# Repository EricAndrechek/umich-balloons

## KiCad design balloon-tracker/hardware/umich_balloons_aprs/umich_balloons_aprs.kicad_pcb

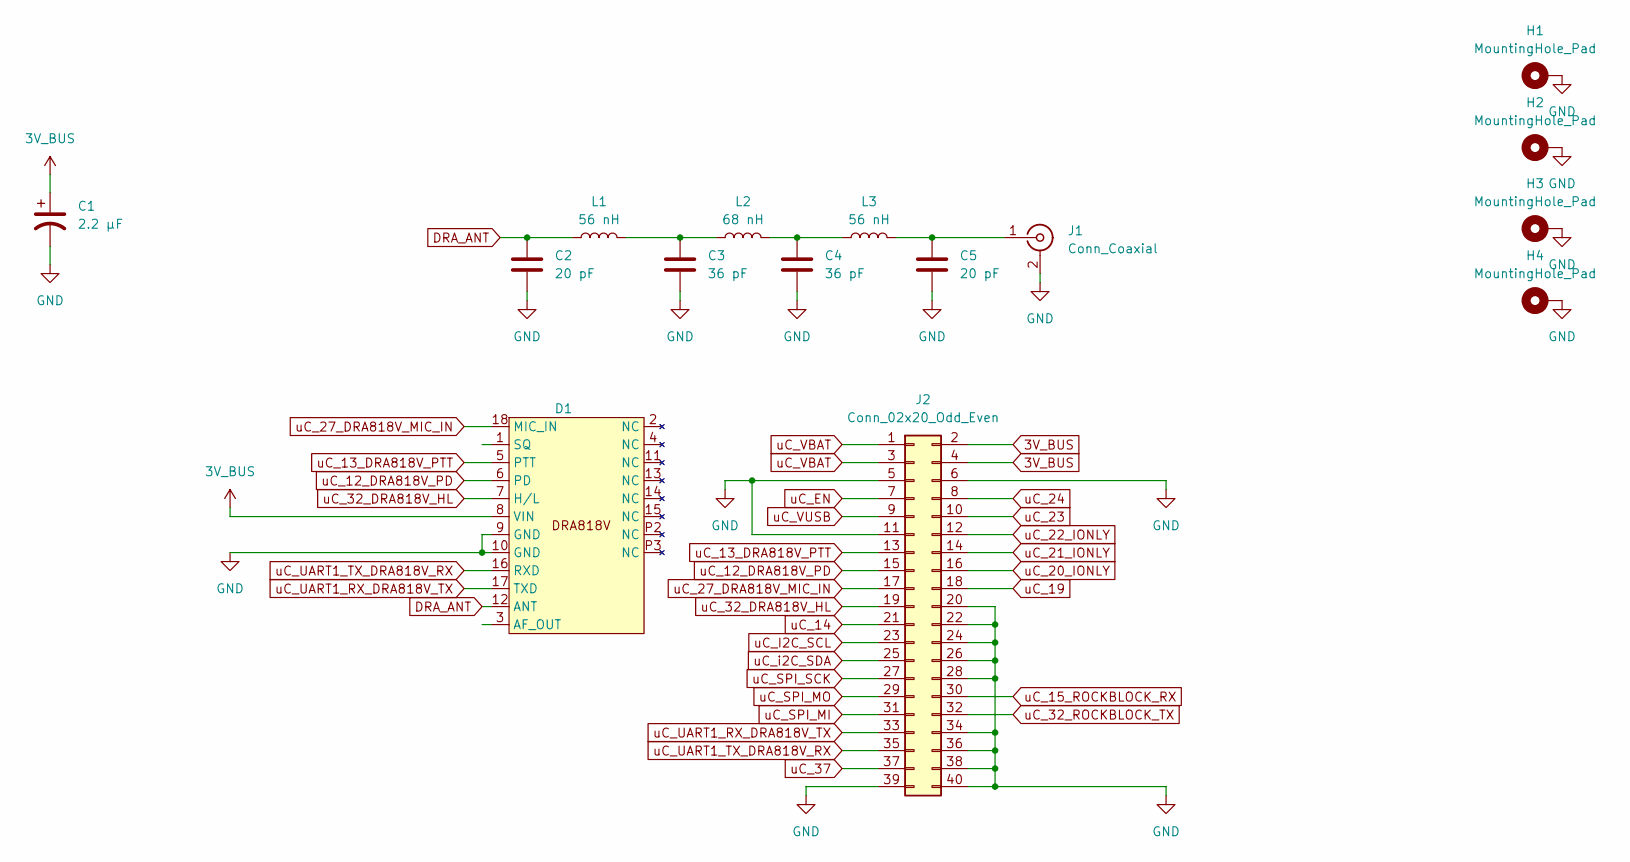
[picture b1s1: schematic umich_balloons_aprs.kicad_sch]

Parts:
C1: 2.2 µF; CP_Radial_D5.0mm_P2.00mm
C2, C5: 20 pF; C_1206_3216Metric_Pad1.33x1.80mm_HandSolder
C3, C4: 36 pF; C_1206_3216Metric_Pad1.33x1.80mm_HandSolder
D1: DORJI_DRA818V
H1, H2, H3, H4: MountingHole_Pad; MountingHole_3.2mm_M3_Pad_Via
J1: Conn_Coaxial; SMA_Wurth_60312002114503_Vertical
J2: Conn_02x20_Odd_Even; PinHeader_2x20_P2.54mm_Vertical
L1, L3: 56 nH; L_1206_3216Metric_Pad1.22x1.90mm_HandSolder
L2: 68 nH; L_1206_3216Metric_Pad1.22x1.90mm_HandSolder

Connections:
3V_BUS: C1.1, D1.8 (VIN), J2.2, J2.4
DRA_ANT: C2.1, D1.12 (ANT), L1.1
GND: C1.2, C2.2, C3.2, C4.2, C5.2, D1.9 (GND), D1.10 (GND), H1.1, H2.1, H3.1, H4.1, J1.2 (Ext), J2.5, J2.6, J2.11, J2.20, J2.22, J2.24, J2.26, J2.28, J2.34, J2.36, J2.38, J2.39, J2.40
unnamed: C3.1, L1.2, L2.1
unnamed: C4.1, L2.2, L3.1
unnamed: C5.1, J1.1 (In), L3.2
uC_12_DRA818V_PD: D1.6 (PD), J2.15
uC_13_DRA818V_PTT: D1.5 (PTT), J2.13
uC_14: J2.21
uC_15_ROCKBLOCK_RX: J2.30
uC_19: J2.18
uC_20_IONLY: J2.16
uC_21_IONLY: J2.14
uC_22_IONLY: J2.12
uC_23: J2.10
uC_24: J2.8
uC_27_DRA818V_MIC_IN: D1.18 (MIC_IN), J2.17
uC_32_DRA818V_HL: D1.7 (H/L), J2.19
uC_32_ROCKBLOCK_TX: J2.32
uC_37: J2.37
uC_EN: J2.7
uC_I2C_SCL: J2.23
uC_SPI_MI: J2.31
uC_SPI_MO: J2.29
uC_SPI_SCK: J2.27
uC_UART1_RX_DRA818V_TX: D1.17 (TXD), J2.33
uC_UART1_TX_DRA818V_RX: D1.16 (RXD), J2.35
uC_VBAT: J2.1, J2.3
uC_VUSB: J2.9
uC_i2C_SDA: J2.25

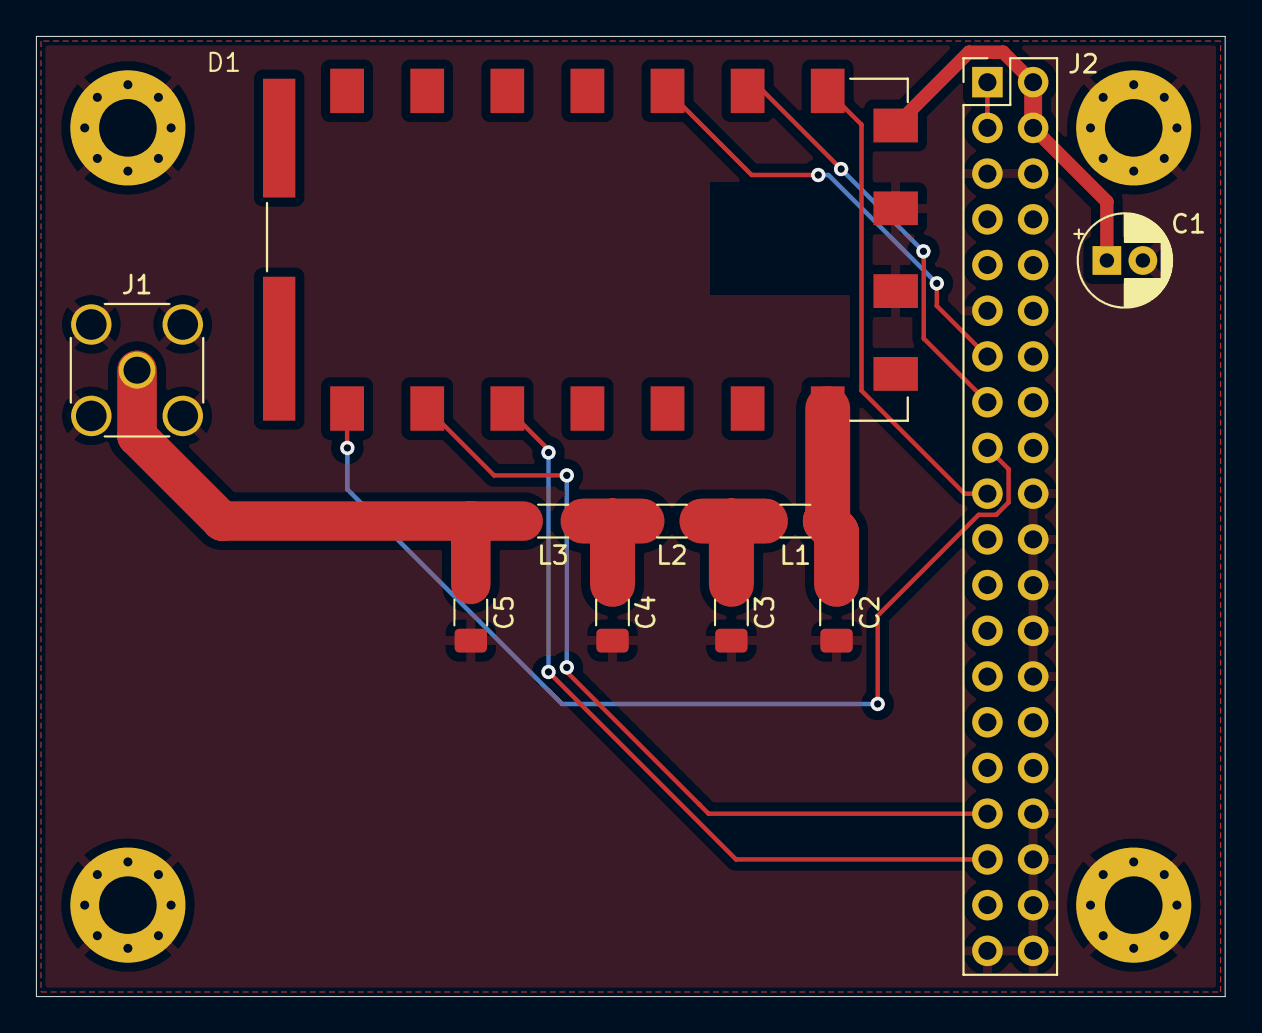
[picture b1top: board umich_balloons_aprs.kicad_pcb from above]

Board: 2 copper layers, 66.0 x 53.3 mm, 15 parts (0 on the bottom side), 13 nets.

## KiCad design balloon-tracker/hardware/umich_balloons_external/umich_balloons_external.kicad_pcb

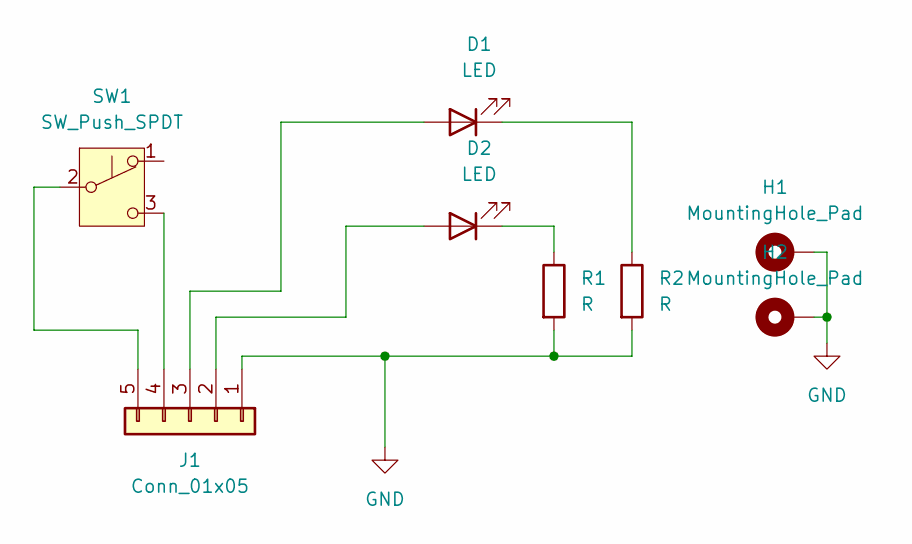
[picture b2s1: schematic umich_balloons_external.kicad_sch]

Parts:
D1, D2: LED; LED_D5.0mm
H1, H2: MountingHole_Pad; MountingHole_3.2mm_M3_Pad_Via
J1: Conn_01x05; JST_EH_B5B-EH-A_1x05_P2.50mm_Vertical
R1, R2: R; R_Axial_DIN0207_L6.3mm_D2.5mm_P10.16mm_Horizontal
SW1: SW_Push_SPDT; PC712A

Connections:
GND: H1.1, H2.1, J1.1, R1.2, R2.2
unnamed: D1.2 (A), J1.3
unnamed: D1.1 (K), R2.1
unnamed: D2.2 (A), J1.2
unnamed: D2.1 (K), R1.1
unnamed: J1.4, SW1.3 (C)
unnamed: J1.5, SW1.2 (B)

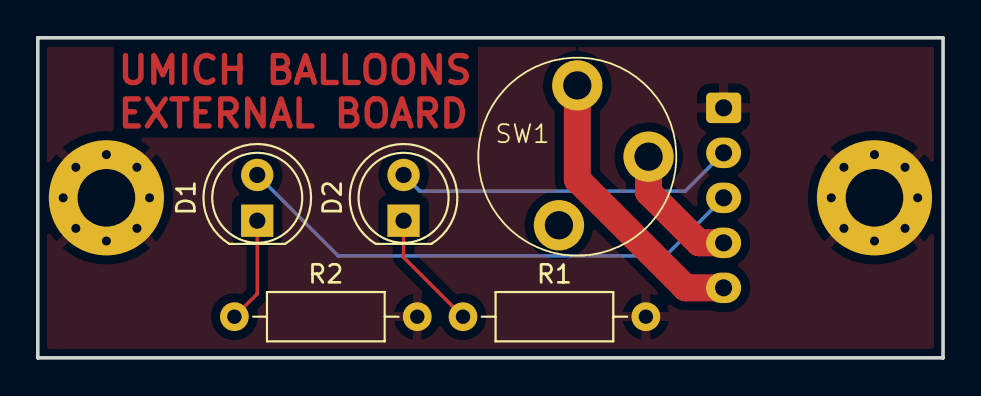
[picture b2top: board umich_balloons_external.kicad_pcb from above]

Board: 2 copper layers, 50.3 x 17.8 mm, 8 parts (1 on the bottom side), 7 nets.

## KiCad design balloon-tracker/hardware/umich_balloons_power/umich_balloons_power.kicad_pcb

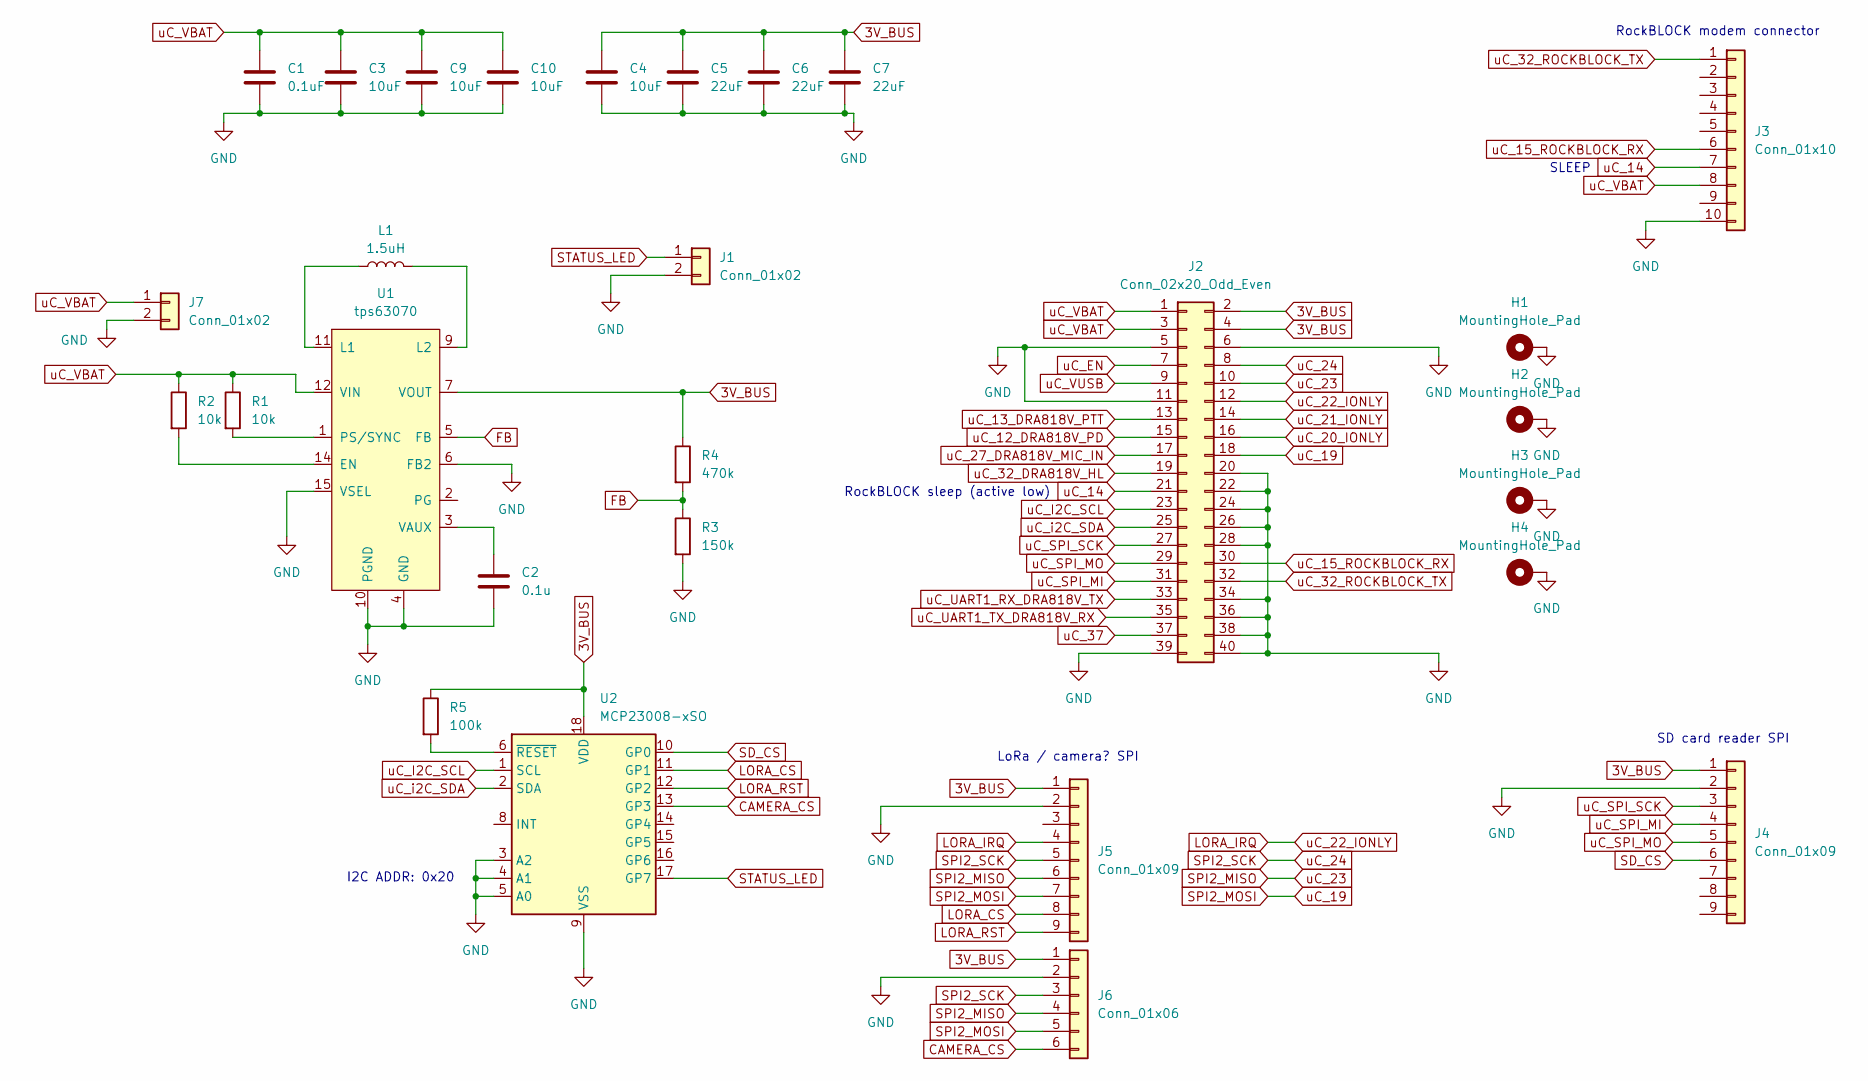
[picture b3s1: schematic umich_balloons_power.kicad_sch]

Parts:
C1: 0.1uF; C_0603_1608Metric; LCSC C14663
C2: 0.1u; C_0805_2012Metric; LCSC C1711
C3, C9, C10: 10uF; C_0805_2012Metric; LCSC C694230
C4: 10uF; C_0603_1608Metric; LCSC C386081
C5, C6, C7: 22uF; C_0805_2012Metric; LCSC C258782
H1, H2, H3, H4: MountingHole_Pad; MountingHole_3.2mm_M3_Pad_Via
J1: Conn_01x02; PinHeader_1x02_P2.54mm_Vertical
J2: Conn_02x20_Odd_Even; PinHeader_2x20_P2.54mm_Vertical
J3: Conn_01x10; Molex_PicoBlade_53047-1010_1x10_P1.25mm_Vertical
J4, J5: Conn_01x09; PinHeader_1x09_P2.54mm_Vertical
J6: Conn_01x06; PinHeader_1x06_P2.54mm_Vertical
J7: Conn_01x02; JST_XH_S2B-XH-A_1x02_P2.50mm_Horizontal
L1: 1.5uH; L_Coilcraft_XxL4020; LCSC C3033018
R1, R2: 10k; R_0603_1608Metric; LCSC C25804
R3: 150k; R_0603_1608Metric; LCSC C22807
R4: 470k; R_0603_1608Metric; LCSC C23178
R5: 100k; R_0603_1608Metric; LCSC C25803
U1: tps63070; VQFN-HR-15; LCSC C109322
U2: MCP23008-xSO; SOIC-18W_7.5x11.6mm_P1.27mm; LCSC C92253

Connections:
3V_BUS: C4.1, C5.1, C6.1, C7.1, J2.2, J2.4, J4.1, J5.1, J6.1, R4.1, R5.1, U1.7 (VOUT), U2.18 (VDD)
CAMERA_CS: J6.6, U2.13 (GP3)
FB: R3.1, R4.2, U1.5 (FB)
GND: C1.2, C2.2, C3.2, C4.2, C5.2, C6.2, C7.2, C9.2, C10.2, H1.1, H2.1, H3.1, H4.1, J1.2, J2.5, J2.6, J2.11, J2.20, J2.22, J2.24, J2.26, J2.28, J2.34, J2.36, J2.38, J2.39, J2.40, J3.10, J4.2, J5.2, J6.2, J7.2, R3.2, U1.4 (GND), U1.6 (FB2), U1.10 (PGND), U1.15 (VSEL), U2.3 (A2), U2.4 (A1), U2.5 (A0), U2.9 (VSS)
LORA_CS: J5.8, U2.11 (GP1)
LORA_IRQ: J2.12, J5.4
LORA_RST: J5.9, U2.12 (GP2)
unnamed: R2.2, U1.14 (EN)
unnamed: L1.1, U1.11 (L1)
unnamed: L1.2, U1.9 (L2)
unnamed: R1.2, U1.1 (PS/SYNC)
unnamed: C2.1, U1.3 (VAUX)
unnamed: R5.2, U2.6 (~RESET)
SD_CS: J4.6, U2.10 (GP0)
SPI2_MISO: J2.10, J5.6, J6.4
SPI2_MOSI: J2.18, J5.7, J6.5
SPI2_SCK: J2.8, J5.5, J6.3
STATUS_LED: J1.1, U2.17 (GP7)
uC_12_DRA818V_PD: J2.15
uC_13_DRA818V_PTT: J2.13
uC_14: J2.21, J3.7
uC_15_ROCKBLOCK_RX: J2.30, J3.6
uC_20_IONLY: J2.16
uC_21_IONLY: J2.14
uC_27_DRA818V_MIC_IN: J2.17
uC_32_DRA818V_HL: J2.19
uC_32_ROCKBLOCK_TX: J2.32, J3.1
uC_37: J2.37
uC_EN: J2.7
uC_I2C_SCL: J2.23, U2.1 (SCL)
uC_SPI_MI: J2.31, J4.4
uC_SPI_MO: J2.29, J4.5
uC_SPI_SCK: J2.27, J4.3
uC_UART1_RX_DRA818V_TX: J2.33
uC_UART1_TX_DRA818V_RX: J2.35
uC_VBAT: C1.1, C3.1, C9.1, C10.1, J2.1, J2.3, J3.8, J7.1, R1.1, R2.1, U1.12 (VIN)
uC_VUSB: J2.9
uC_i2C_SDA: J2.25, U2.2 (SDA)

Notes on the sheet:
I2C ADDR: 0x20
RockBLOCK modem connector
RockBLOCK sleep (active low)
LoRa / camera? SPI
SLEEP
SD card reader SPI

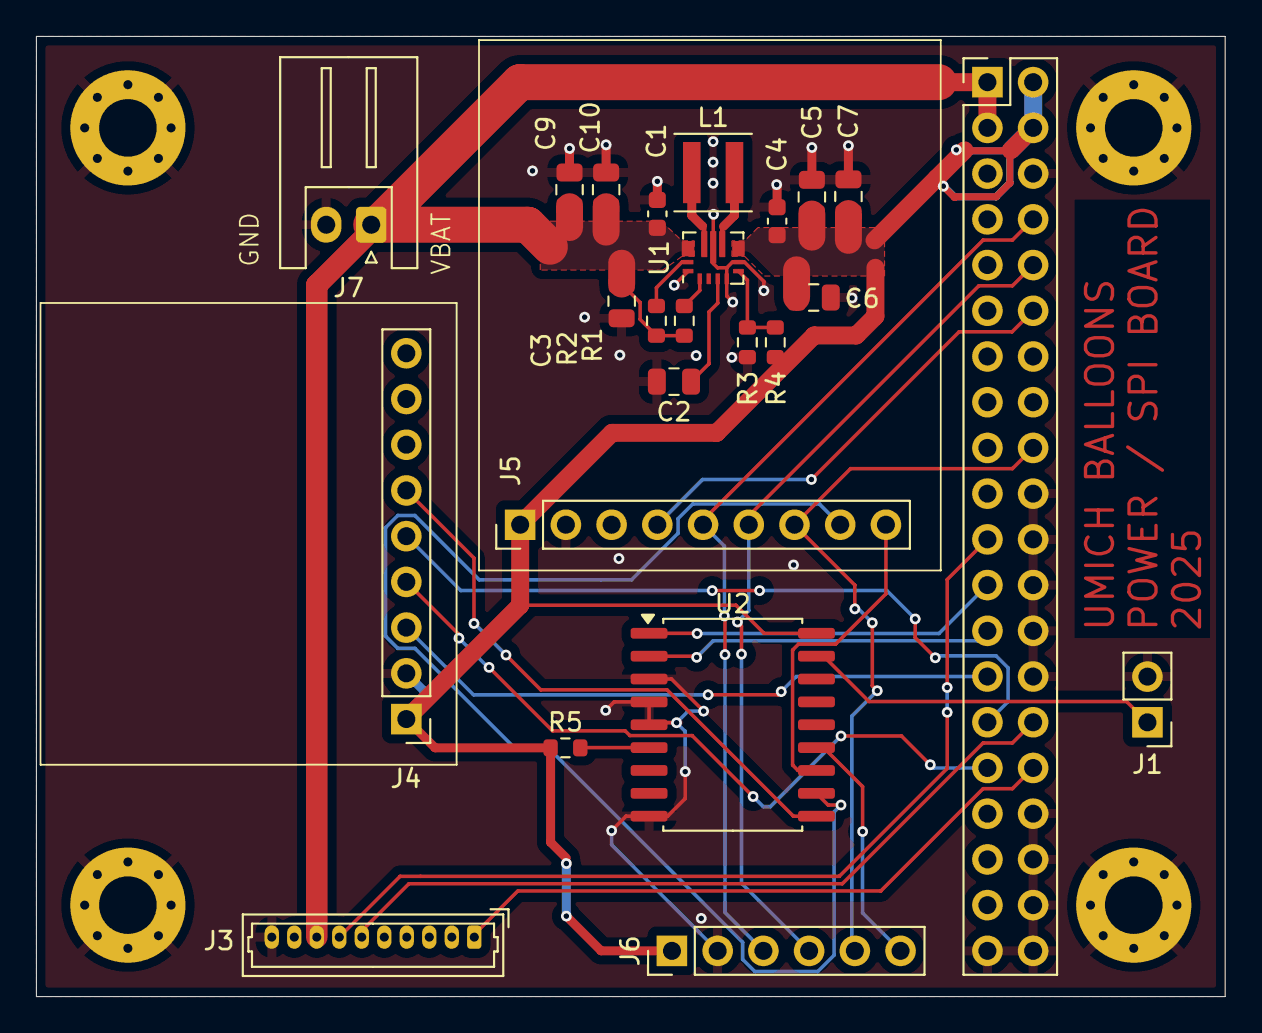
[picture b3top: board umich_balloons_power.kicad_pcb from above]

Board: 2 copper layers, 66.0 x 53.3 mm, 28 parts (0 on the bottom side), 27 nets.

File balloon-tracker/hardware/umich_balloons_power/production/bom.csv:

Designator,Footprint,Quantity,Value,LCSC Part #
C1,0603,1,0.1uF,C14663
"C10, C3, C9",0805,3,10uF,C694230
C2,0805,1,0.1u,C1711
C4,0603,1,10uF,C386081
"C5, C6, C7",0805,3,22uF,C258782
L1,L_Coilcraft_XxL4020,1,1.5uH,C3033018
"R1, R2",0603,2,10k,C25804
R3,0603,1,150k,C22807
R4,0603,1,470k,C23178
R5,0603,1,100k,C25803
U1,VQFN-HR-15,1,tps63070,C109322
U2,SOIC-18W_7.5x11.6mm_P1.27mm,1,MCP23008-xSO,C92253

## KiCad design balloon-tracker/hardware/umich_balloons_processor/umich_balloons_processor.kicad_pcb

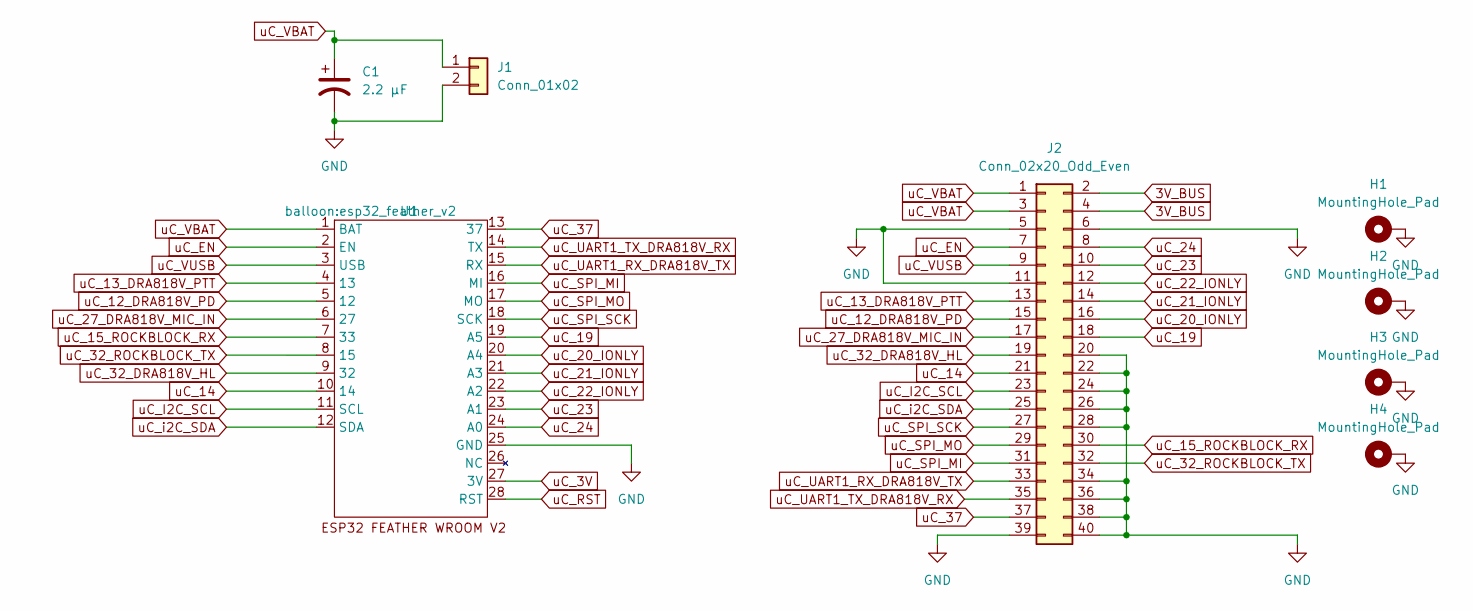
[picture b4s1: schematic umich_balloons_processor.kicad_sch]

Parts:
C1: 2.2 µF; CP_Radial_D5.0mm_P2.00mm
H1, H2, H3, H4: MountingHole_Pad; MountingHole_3.2mm_M3_Pad_Via
J1: Conn_01x02; JST_EH_S2B-EH_1x02_P2.50mm_Horizontal
J2: Conn_02x20_Odd_Even; PinHeader_2x20_P2.54mm_Vertical
U1: esp32_feather_v2

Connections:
3V_BUS: J2.2, J2.4
GND: C1.2, H1.1, H2.1, H3.1, H4.1, J1.2, J2.5, J2.6, J2.11, J2.20, J2.22, J2.24, J2.26, J2.28, J2.34, J2.36, J2.38, J2.39, J2.40, U1.25 (GND)
uC_3V: U1.27 (3V)
uC_12_DRA818V_PD: J2.15, U1.5 (12)
uC_13_DRA818V_PTT: J2.13, U1.4 (13)
uC_14: J2.21, U1.10 (14)
uC_15_ROCKBLOCK_RX: J2.30, U1.7 (33)
uC_19: J2.18, U1.19 (A5)
uC_20_IONLY: J2.16, U1.20 (A4)
uC_21_IONLY: J2.14, U1.21 (A3)
uC_22_IONLY: J2.12, U1.22 (A2)
uC_23: J2.10, U1.23 (A1)
uC_24: J2.8, U1.24 (A0)
uC_27_DRA818V_MIC_IN: J2.17, U1.6 (27)
uC_32_DRA818V_HL: J2.19, U1.9 (32)
uC_32_ROCKBLOCK_TX: J2.32, U1.8 (15)
uC_37: J2.37, U1.13 (37)
uC_EN: J2.7, U1.2 (EN)
uC_I2C_SCL: J2.23, U1.11 (SCL)
uC_RST: U1.28 (RST)
uC_SPI_MI: J2.31, U1.16 (MI)
uC_SPI_MO: J2.29, U1.17 (MO)
uC_SPI_SCK: J2.27, U1.18 (SCK)
uC_UART1_RX_DRA818V_TX: J2.33, U1.15 (RX)
uC_UART1_TX_DRA818V_RX: J2.35, U1.14 (TX)
uC_VBAT: C1.1, J1.1, J2.1, J2.3, U1.1 (BAT)
uC_VUSB: J2.9, U1.3 (USB)
uC_i2C_SDA: J2.25, U1.12 (SDA)

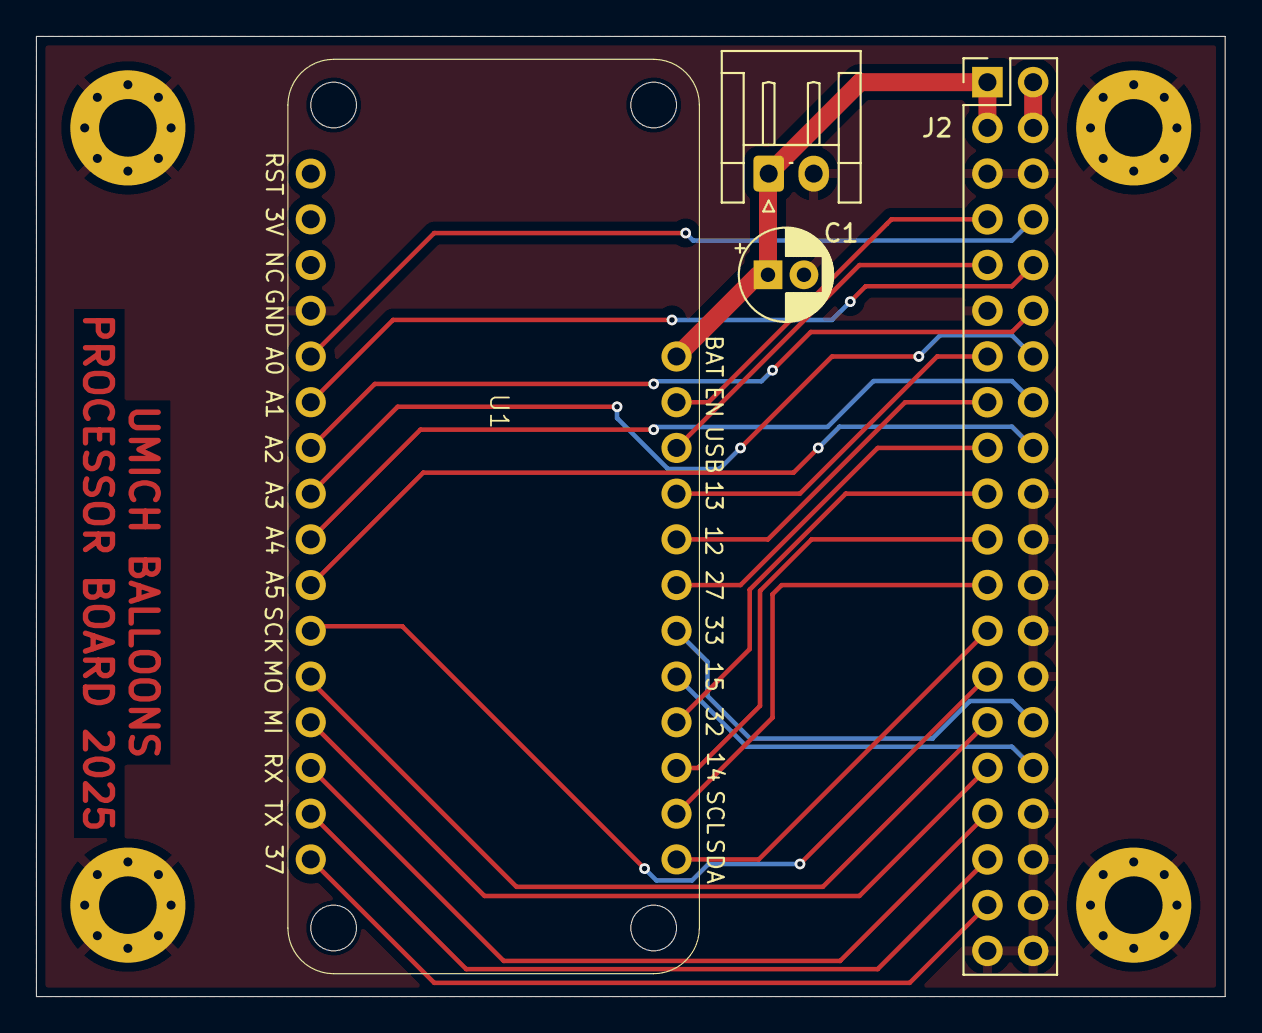
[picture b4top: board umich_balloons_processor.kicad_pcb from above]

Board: 2 copper layers, 66.0 x 53.3 mm, 8 parts (0 on the bottom side), 26 nets.

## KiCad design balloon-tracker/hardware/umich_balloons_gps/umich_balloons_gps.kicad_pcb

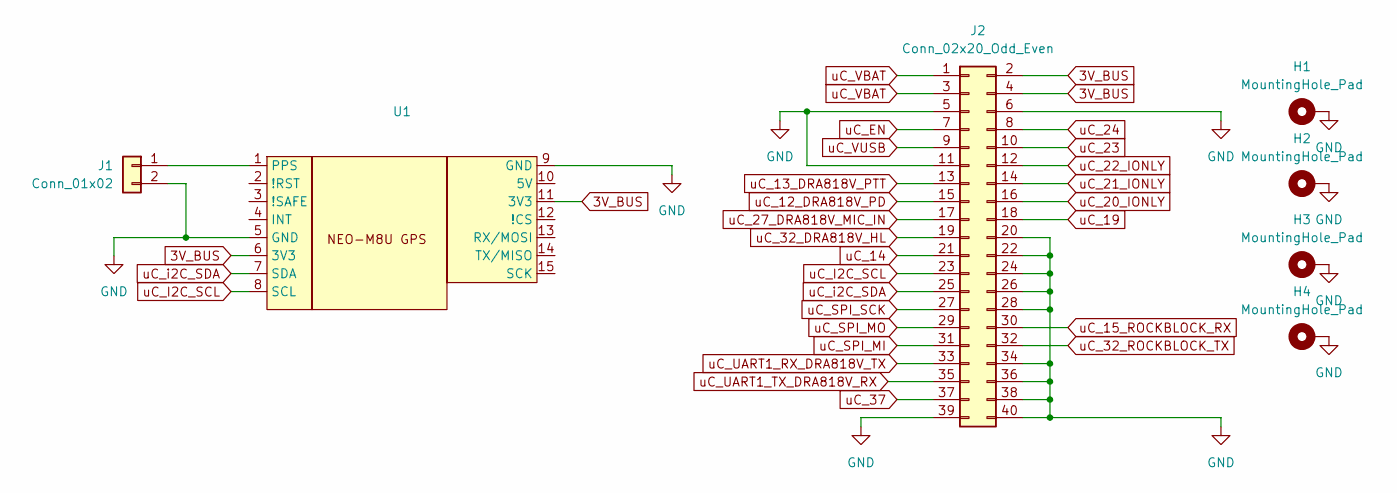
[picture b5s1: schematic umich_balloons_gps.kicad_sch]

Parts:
H1, H2, H3, H4: MountingHole_Pad; MountingHole_3.2mm_M3_Pad_Via
J1: Conn_01x02; JST_EH_S2B-EH_1x02_P2.50mm_Horizontal
J2: Conn_02x20_Odd_Even; PinHeader_2x20_P2.54mm_Vertical
U1: sparkfun_neo-m8u

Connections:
3V_BUS: J2.2, J2.4, U1.6 (3V3), U1.11 (3V3)
GND: H1.1, H2.1, H3.1, H4.1, J1.2, J2.5, J2.6, J2.11, J2.20, J2.22, J2.24, J2.26, J2.28, J2.34, J2.36, J2.38, J2.39, J2.40, U1.5 (GND), U1.9 (GND)
unnamed: J1.1, U1.1 (PPS)
uC_12_DRA818V_PD: J2.15
uC_13_DRA818V_PTT: J2.13
uC_14: J2.21
uC_15_ROCKBLOCK_RX: J2.30
uC_19: J2.18
uC_20_IONLY: J2.16
uC_21_IONLY: J2.14
uC_22_IONLY: J2.12
uC_23: J2.10
uC_24: J2.8
uC_27_DRA818V_MIC_IN: J2.17
uC_32_DRA818V_HL: J2.19
uC_32_ROCKBLOCK_TX: J2.32
uC_37: J2.37
uC_EN: J2.7
uC_I2C_SCL: J2.23, U1.8 (SCL)
uC_SPI_MI: J2.31
uC_SPI_MO: J2.29
uC_SPI_SCK: J2.27
uC_UART1_RX_DRA818V_TX: J2.33
uC_UART1_TX_DRA818V_RX: J2.35
uC_VBAT: J2.1, J2.3
uC_VUSB: J2.9
uC_i2C_SDA: J2.25, U1.7 (SDA)

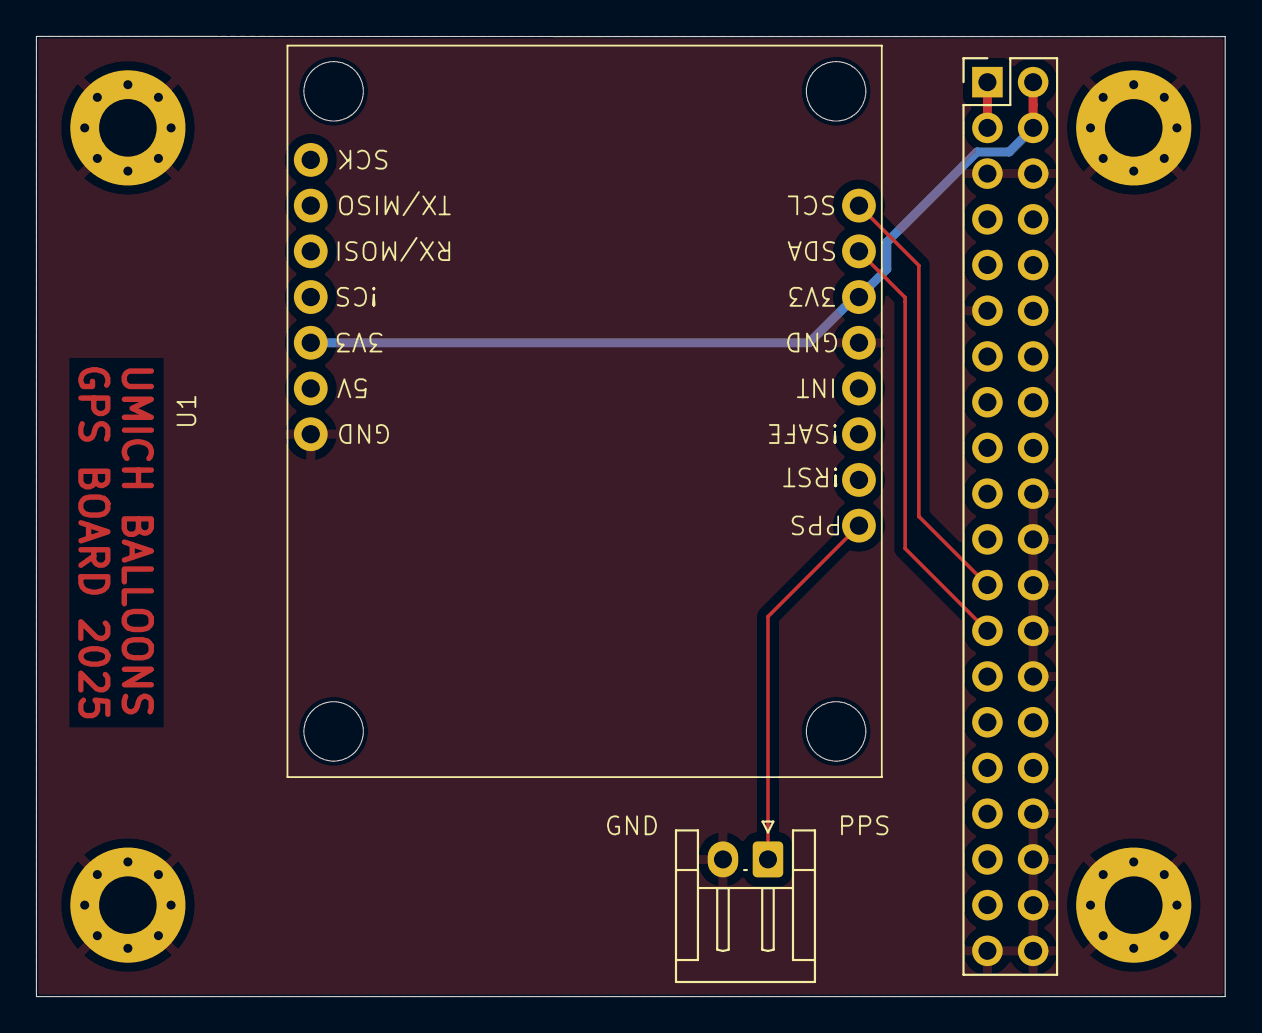
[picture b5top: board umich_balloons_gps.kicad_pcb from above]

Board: 2 copper layers, 66.0 x 53.3 mm, 7 parts (0 on the bottom side), 6 nets.

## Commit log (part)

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2025-02-18 initial repo structure
2025-03-19 Implement high-altitude balloon tracking system
    This commit implements a real-time tracking system for high-altitude balloons, integrating data from various sources (MQTT, APRS-IS) into a unified platform. The system includes a FastAPI backend for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
    Key features:
    - Real-time tracking of balloon positions and telemetry
    - Support for multiple data sources (MQTT, APRS-IS)
    - Data validation and deduplication
    - Two-way synchronization between the server and ground stations/chase vehicles
2025-03-21 progress so far, about to force over jules
2025-03-21 no more ai
2025-03-27 most backend pieces in place, integration h3ll left
2025-03-31 almost working backend all together
2025-04-01 building backend models for auto-parsing
2025-04-02 iridium backend done, aprs and lora to go
2025-04-02 iridium and lora done
2025-04-02 working lora, aprs, and iridium (just not APRS-IS)
2025-04-03 computer crashing, saving h3 and frontend
2025-04-08 almost there...
2025-04-08 working but lines are split, trying to combine
2025-04-08 working barebones pi logging
2025-07-06 pushing last changes never added for own reference
2026-04-08 go version of api with more robust test code
2026-04-08 backend api switched to running on cloudflare workers
2026-04-08 renamed umich balloons project name for wrangler
2026-04-08 enabling default url and logs
2026-04-09 tweaking wrangler.toml to match cf dashboard config
2026-04-09 fixing t value in json, sondehub metadata, more robust testing
2026-04-09 ground-station: rewrite entire python and sdm/fullpageos to packer and go binary
2026-04-09 Bump the go_modules group across 1 directory with 3 updates
    Bumps the go_modules group with 1 update in the /ground-station/umbgs directory: [github.com/quic-go/quic-go](https://github.com/quic-go/quic-go).
    Updates `github.com/quic-go/quic-go` from 0.48.2 to 0.57.0
    - [Release notes](https://github.com/quic-go/quic-go/releases)
    - [Commits](https://github.com/quic-go/quic-go/compare/v0.48.2...v0.57.0)
    Updates `golang.org/x/crypto` from 0.26.0 to 0.41.0
    - [Commits](https://github.com/golang/crypto/compare/v0.26.0...v0.41.0)
2026-04-09 debugging packer build errors
2026-04-09 adjusting go version for cicd
2026-04-09 packer reading raspi os image had wrong extension
2026-04-09 packer arm changing to reuse instead or resize
2026-04-09 fix packer, need resize method for new partition
2026-04-09 defering data overlay fs setup to install script, not packer
2026-04-09 cutting out gpsd-clients to remove python deps
2026-04-09 adding plymouth theme for boot
2026-04-09 wrong path for uploading to releases
2026-04-09 permissions wrong for action to upload img to releases
2026-04-09 need to pre-create user and allow auto login
2026-04-09 disabling ro overlay for now
2026-04-09 tmp overlay after boot
2026-04-09 adding debugging to server to see why no sondehub
2026-04-09 iridium and lora use compact format with 1/100th alts
2026-04-10 properly handling weird time format from json
2026-04-10 keep second precision from lora/iridium rx
2026-04-10 debugging new gs failing to boot service
2026-04-10 launch into shell properly
2026-04-10 plymouth issues
2026-04-10 enable ssh for debugging
2026-04-10 new api code to be (hopefully) more robust and simpler
2026-04-10 trying a different method for building images
2026-04-10 semi working version, including brians code and hw
2026-04-11 Bump golang.org/x/crypto
    Bumps the go_modules group with 1 update in the /ground-station/umbgs directory: [golang.org/x/crypto](https://github.com/golang/crypto).
    Updates `golang.org/x/crypto` from 0.41.0 to 0.45.0
    - [Commits](https://github.com/golang/crypto/compare/v0.41.0...v0.45.0)
    ---
    updated-dependencies:
    - dependency-name: golang.org/x/crypto
2026-04-11 ground-station: install iptables + seed captive portal dnsmasq config
    Two fixes for the field-deployed Pi image:
    1. Pi OS Bookworm ships nftables by default and does NOT install
    iptables transitively through network-manager, so ensureAPFirewall
    was logging "iptables not found" and the AP FORWARD drop rule never
    got installed — meaning phones joining the hotspot could tunnel
    traffic out the Pi's uplink. Add iptables to install.sh's apt list.
2026-04-11 ground-station: persist update check, diagnose captive portal + apply flow
    Four fixes for the field UX:
    1. Captive portal diagnostics. Bind :80 synchronously so a bind failure
    surfaces as a distinct log line at startup instead of hiding in a
    goroutine, and add logCaptivePortalHealth() that reports whether the
    dnsmasq drop-in file is on disk and whether a running dnsmasq is
    actually using it. That turns "portal doesn't pop up" into a log
2026-04-11 ground-station: defer captive portal health check to steady state
    The startup health check was producing a false-positive "no dnsmasq
    process found" warning: NM hadn't yet activated the AP hotspot when
    umbgs started, so the check fired before dnsmasq was even spawned.
    Run the initial check in a 20s-delayed goroutine instead, and also
    re-run it on the existing 5-minute sync tick so a late hotspot
    activation (or a post-install drop-in write that hadn't taken effect
2026-04-11 dashboard: cap contact distance at 1500 km to drop bogus GPS readings
    Bad lat/lon decoded from a corrupt LoRa packet was producing 3000+ km
    "farthest contacts" entries (e.g. KF8ABL-12 reporting positions in the
    mid-Atlantic). Cap haversine output at 1500 km — well above the ~1100 km
    amateur LoRa world record and the ~620 km APRS line-of-sight horizon
    from a 30 km balloon — and null the field above the cap. The contact
    row still inserts so packet counts and timelines stay accurate; only
2026-04-11 dashboard: filter leaderboard by balloon and modulation
    Adds two dropdowns above the farthest-contacts table — one for balloon
    callsign, one for modulation (APRS / LoRa / etc.) — so you can see, for
    example, "best LoRa contacts on KF8ABL-12" instead of only the global
    top per uploader. Filter state lives in the launch page so the existing
    poll loop picks up the current selection on every refresh; an effect
    re-fires refresh() when the user flips a dropdown.
2026-04-16 build(deps): bump hono
    Bumps the npm_and_yarn group with 1 update in the /dashboard directory: [hono](https://github.com/honojs/hono).
    Updates `hono` from 4.12.12 to 4.12.14
    - [Release notes](https://github.com/honojs/hono/releases)
    - [Commits](https://github.com/honojs/hono/compare/v4.12.12...v4.12.14)
    ---
    updated-dependencies:
2026-05-07 build(deps): bump hono
    Bumps the npm_and_yarn group with 1 update in the /dashboard directory: [hono](https://github.com/honojs/hono).
    Updates `hono` from 4.12.12 to 4.12.16
    - [Release notes](https://github.com/honojs/hono/releases)
    - [Commits](https://github.com/honojs/hono/compare/v4.12.12...v4.12.16)
    ---
    updated-dependencies:
2026-05-09 build(deps): bump hono
    Bumps the npm_and_yarn group with 1 update in the /dashboard directory: [hono](https://github.com/honojs/hono).
    Updates `hono` from 4.12.12 to 4.12.18
    - [Release notes](https://github.com/honojs/hono/releases)
    - [Commits](https://github.com/honojs/hono/compare/v4.12.12...v4.12.18)
    ---
    updated-dependencies:
